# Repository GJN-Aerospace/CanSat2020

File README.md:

# CanSat 2020

GitHub repository for CanSat 2020 competitoin. You can find here a design of **our CanSat probe PKII** but also our Arduino code for openCanSat kit. 

## Probe

We designed our own probe. It name is "Cosmic Song II" or for short just CSII (in czech Píseň kosmická II, PKII). But we have in Software section a code for our backup probe from openCanSat kit. 

## GroundStation

We use as a our Ground Station a baseStation from openCanSat kit. So you can find in Software folder our code for it. 

### Links

* [openCanSat](http://kit.sciencein.cz)

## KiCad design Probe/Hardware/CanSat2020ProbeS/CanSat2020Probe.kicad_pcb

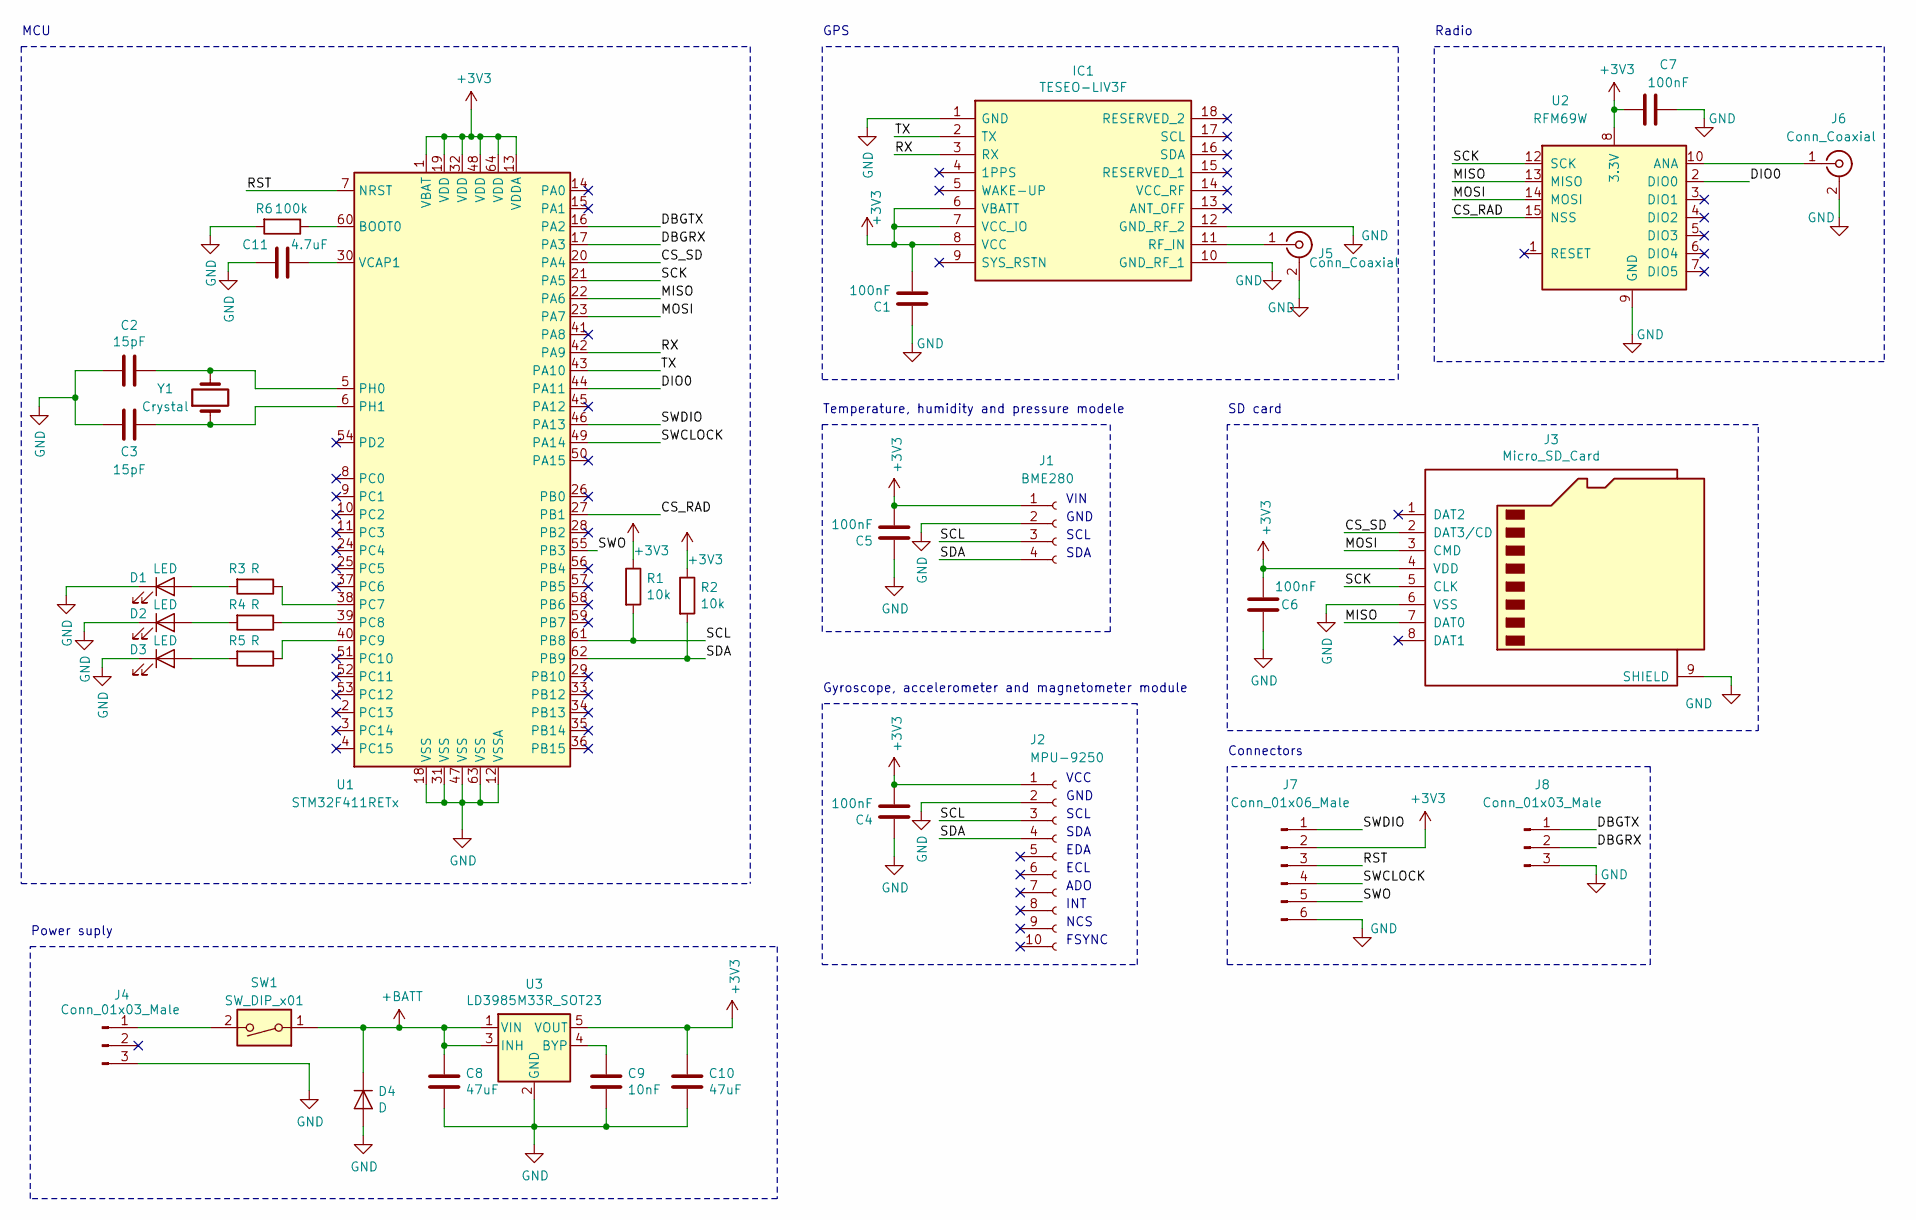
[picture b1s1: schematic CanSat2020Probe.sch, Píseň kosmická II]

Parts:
C1, C4, C5, C6, C7: 100nF; C_0805_2012Metric
C2, C3: 15pF; C_0805_2012Metric
C8, C10: 47uF; CP_Radial_D5.0mm_P2.00mm
C9: 10nF; C_0805_2012Metric
C11: 4.7uF; C_0805_2012Metric
D1, D2, D3: LED; LED_1206_3216Metric
D4: D; D_DO-41_SOD81_P10.16mm_Horizontal
IC1: TESEO-LIV3F; SON110P970X1010X230-18N; Manufacturer_Part_Number TESEO-LIV3F; Mouser Part Number 511-TESEO-LIV3F
J1: BME280
J2: MPU-9250; MPU-9250-4pin
J3: Micro_SD_Card; microSD_HC_Wuerth_693072010801
J4: Conn_01x03_Male; Batt_PHS_Hor_Long18mm
J5, J6: Conn_Coaxial; U.FL_Hirose_U.FL-R-SMT-1_Vertical
J7: Conn_01x06_Male; PinHeader_1x06_P2.54mm_Vertical
J8: Conn_01x03_Male; PinHeader_1x03_P2.54mm_Vertical
R1, R2: 10k; R_0805_2012Metric
R3, R4, R5: R; R_0805_2012Metric
R6: 100k; R_0805_2012Metric
SW1: SW_DIP_x01; Sw_ESP2010
U1: STM32F411RETx; LQFP-64_10x10mm_P0.5mm
U2: RFM69W; HOPERF_RFM69HW
U3: LD3985M33R_SOT23; SOT-23-5_HandSoldering
Y1: Crystal; Crystal_SMD_HC49-SD

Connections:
+3V3: C1.1, C4.1, C5.1, C6.1, C7.1, C10.1, IC1.6 (VBATT), IC1.7 (VCC_IO), IC1.8 (VCC), J1.1, J2.1, J3.4 (VDD), J7.2, R1.1, R2.1, U1.1 (VBAT), U1.13 (VDDA), U1.19 (VDD), U1.32 (VDD), U1.48 (VDD), U1.64 (VDD), U2.8 (3.3V), U3.5 (VOUT)
+BATT: C8.1, D4.1 (K), SW1.1, U3.1 (VIN), U3.3 (INH)
/CS_RAD: U1.27 (PB1), U2.15 (NSS)
/CS_SD: J3.2 (DAT3/CD), U1.20 (PA4)
/DBGRX: J8.2, U1.17 (PA3)
/DBGTX: J8.1, U1.16 (PA2)
/DIO0: U1.44 (PA11), U2.2 (DIO0)
/MISO: J3.7 (DAT0), U1.22 (PA6), U2.13 (MISO)
/MOSI: J3.3 (CMD), U1.23 (PA7), U2.14 (MOSI)
/RST: J7.3, U1.7 (NRST)
/RX: IC1.3 (RX), U1.42 (PA9)
/SCK: J3.5 (CLK), U1.21 (PA5), U2.12 (SCK)
/SCL: J1.3, J2.3, R1.2, U1.61 (PB8)
/SDA: J1.4, J2.4, R2.2, U1.62 (PB9)
/SWCLOCK: J7.4, U1.49 (PA14)
/SWDIO: J7.1, U1.46 (PA13)
/SWO: J7.5, U1.55 (PB3)
/TX: IC1.2 (TX), U1.43 (PA10)
GND: C1.2, C2.2, C3.1, C4.2, C5.2, C6.2, C7.2, C8.2, C9.2, C10.2, C11.2, D1.1 (K), D2.1 (K), D3.1 (K), D4.2 (A), IC1.1 (GND), IC1.10 (GND_RF_1), IC1.12 (GND_RF_2), J1.2, J2.2, J3.6 (VSS), J3.9 (SHIELD), J4.3, J5.2 (Ext), J6.2 (Ext), J7.6, J8.3, R6.2, U1.12 (VSSA), U1.18 (VSS), U1.31 (VSS), U1.47 (VSS), U1.63 (VSS), U2.9 (GND), U2.11 (GND), U3.2 (GND)
unnamed: C2.1, U1.5 (PH0), Y1.2
unnamed: C3.2, U1.6 (PH1), Y1.1
unnamed: C9.1, U3.4 (BYP)
unnamed: C11.1, U1.30 (VCAP1)
unnamed: D1.2 (A), R3.2
unnamed: D2.2 (A), R4.2
unnamed: D3.2 (A), R5.2
unnamed: IC1.11 (RF_IN), J5.1 (In)
unnamed: J4.1, SW1.2
unnamed: J6.1 (In), U2.10 (ANA)
unnamed: R3.1, U1.38 (PC7)
unnamed: R4.1, U1.39 (PC8)
unnamed: R5.1, U1.40 (PC9)
unnamed: R6.1, U1.60 (BOOT0)

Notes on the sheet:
VIN
GND
SCL
SDA
VCC
GND
SCL
EDA
ECL
ADO
INT
NCS
FSYNC
MCU
GPS
Radio
SD card
Temperature, humidity and pressure modele
Gyroscope, accelerometer and magnetometer module
Power suply
Connectors

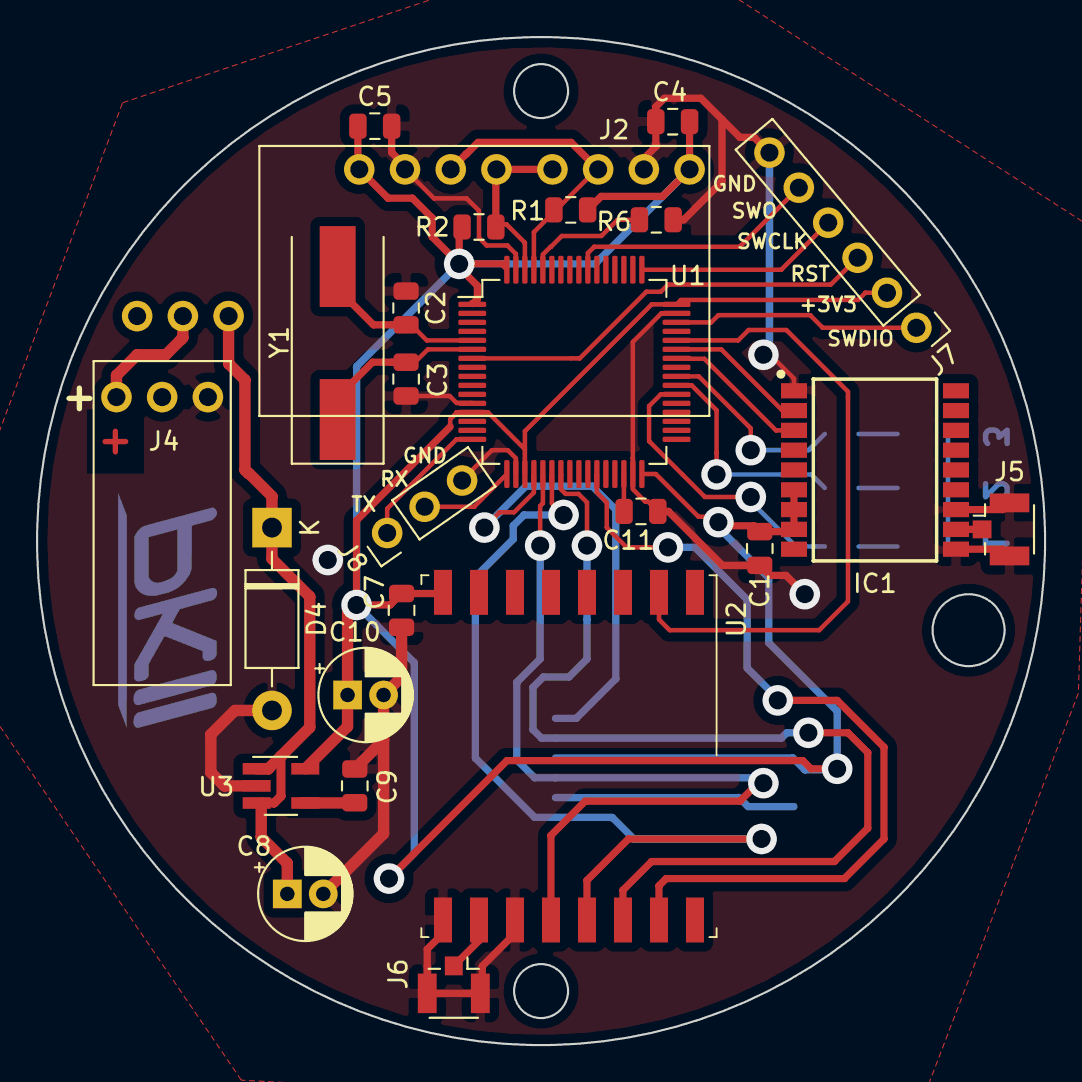
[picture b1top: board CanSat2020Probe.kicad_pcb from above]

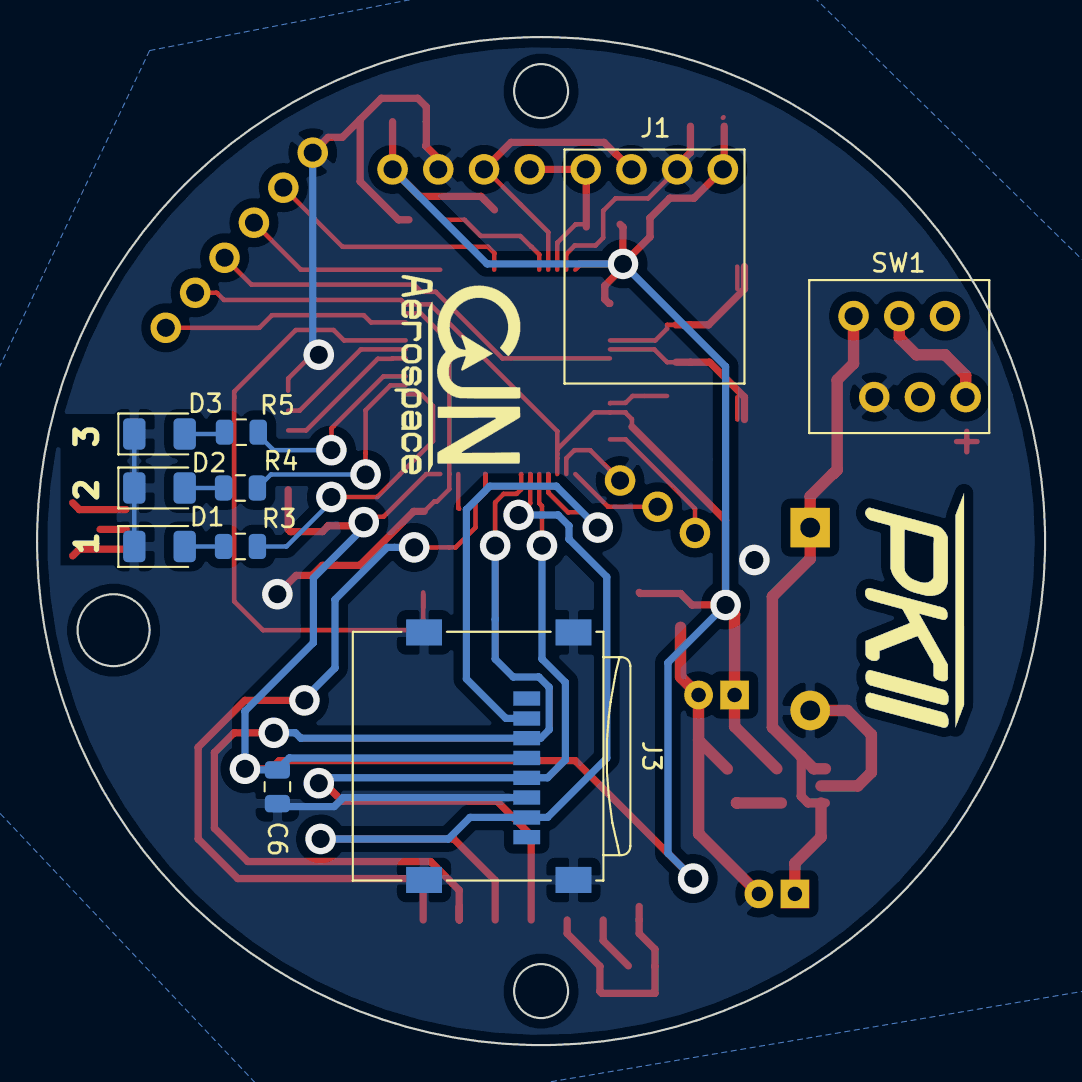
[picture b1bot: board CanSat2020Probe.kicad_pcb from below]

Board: 2 copper layers, 56.0 x 56.0 mm, 35 parts (10 on the bottom side), 33 nets.

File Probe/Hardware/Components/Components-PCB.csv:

"Id";"Designator";"Package";"Quantity";"Designation";"Supplier and ref";
1;"G***";"gjna";1;"LOGO";;;
2;"G***";"pkiiB";1;"LOGO";;;
3;"G***";"pkii";1;"LOGO";;;
4;"J4";"Batt_PHS_Hor_Long18mm";1;"Conn_01x03_Male";;;
5;"U2";"HOPERF_RFM69HW";1;"RFM69W";;;
6;"J3";"microSD_HC_Wuerth_693072010801";1;"Micro_SD_Card";;;
7;"J5,J6";"U.FL_Hirose_U.FL-R-SMT-1_Vertical";2;"Conn_Coaxial";;;
8;"J8";"PinHeader_1x03_P2.54mm_Vertical";1;"Conn_01x03_Male";;;
9;"J7";"PinHeader_1x06_P2.54mm_Vertical";1;"Conn_01x06_Male";;;
10;"C7,C4,C1,C5,C6";"C_0805_2012Metric";5;"100nF";;;
11;"R1,R2";"R_0805_2012Metric";2;"10k";;;
12;"D4";"D_DO-41_SOD81_P10.16mm_Horizontal";1;"D";;;
13;"C8,C10";"CP_Radial_D5.0mm_P2.00mm";2;"47uF";;;
14;"C9";"C_0805_2012Metric";1;"10nF";;;
15;"C2,C3";"C_0805_2012Metric";2;"15pF";;;
16;"C11";"C_0805_2012Metric";1;"4.7uF";;;
17;"D1,D2,D3";"LED_1206_3216Metric";3;"LED";;;
18;"IC1";"SON110P970X1010X230-18N";1;"TESEO-LIV3F";;;
19;"J1";"BME280";1;"BME280";;;
20;"R3,R4,R5";"R_0805_2012Metric";3;"R";;;
21;"R6";"R_0805_2012Metric";1;"100k";;;
22;"U1";"LQFP-64_10x10mm_P0.5mm";1;"STM32F411RETx";;;
23;"Y1";"Crystal_SMD_HC49-SD";1;"Crystal";;;
24;"J2";"MPU-9250-4pin";1;"MPU-9250";;;
25;"SW1";"Sw_ESP2010";1;"SW_DIP_x01";;;
26;"U3";"SOT-23-5_HandSoldering";1;"LD3985M33R_SOT23";;;

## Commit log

2019-10-28 přidání KiCad souboru
2019-10-28 Rename README.txt to README.md
2019-12-23 Add components descriptions
2019-12-30 Reorganisation
2020-01-01 addition of new components
2020-01-03 new parts and reorganisation
2020-01-04 upadte
2020-01-07 Impprovements
2020-01-12 minor changes
2020-01-25 small changes
2020-01-26 improuvements
2020-02-29 minor improvements
